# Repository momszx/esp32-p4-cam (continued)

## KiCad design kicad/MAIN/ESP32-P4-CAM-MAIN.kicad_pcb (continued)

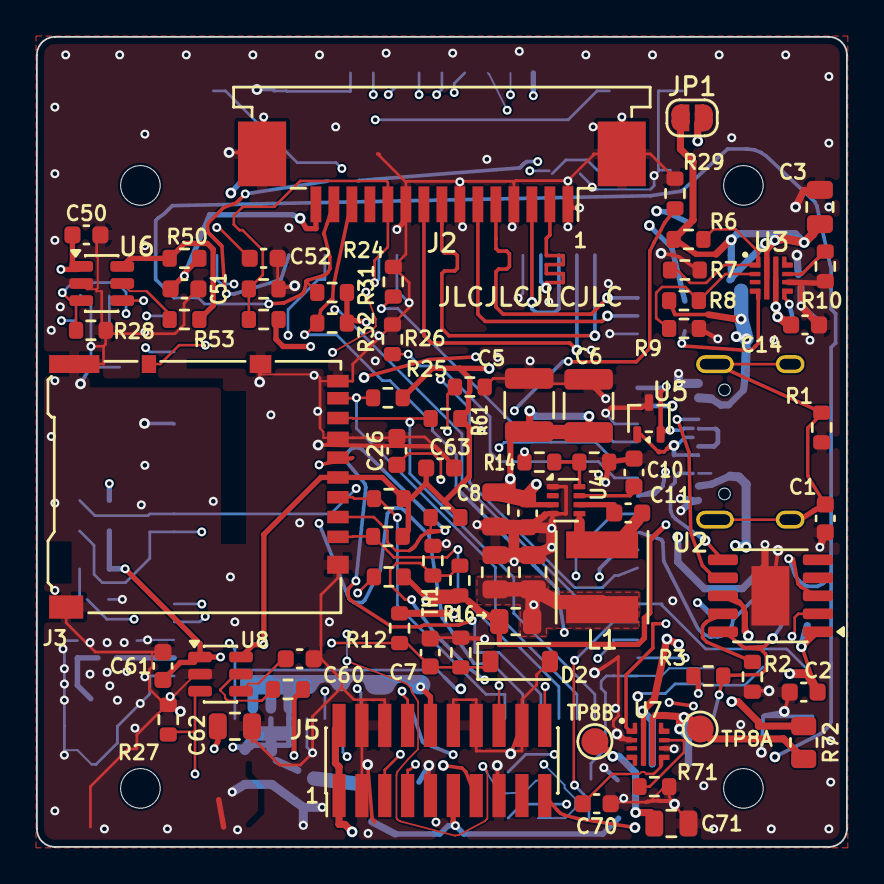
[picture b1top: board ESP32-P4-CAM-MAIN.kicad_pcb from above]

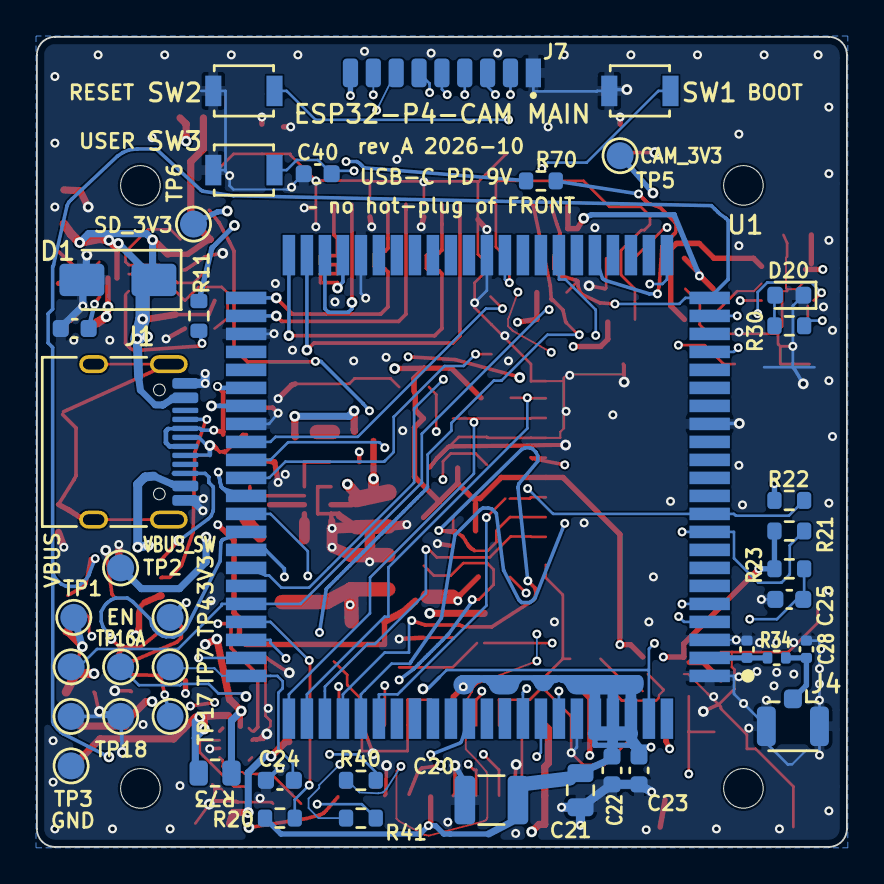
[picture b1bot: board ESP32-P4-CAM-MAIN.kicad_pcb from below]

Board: 4 copper layers, 45.0 x 45.0 mm, 120 parts (42 on the bottom side), 77 nets.

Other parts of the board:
MH1, MH2, MH3, MH4: MountingHole_2.2mm_M2

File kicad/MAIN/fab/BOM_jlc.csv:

Comment,Designator,Footprint,LCSC
4.7nF 200V X7R ±10% 0603,C1,C_0603_1608Metric,C596328
1uF 50V X5R ±10% 0603,"C2,C24,C25,C50,C51",C_0603_1608Metric,C15849
4.7uF 50V X5R ±10% 0805,C3,C_0805_2012Metric,C98192
1nF 50V X7R ±10% 0603,"C4,C52",C_0603_1608Metric,C1588
22uF 25V X5R ±10% 1210,"C5,C6",C_1210_3225Metric,C52306
100nF 50V X7R ±10% 0603,"C7,C9,C11,C22,C23,C26,C40",C_0603_1608Metric,C14663
10uF 25V X5R ±10% 0805,"C8,C21",C_0805_2012Metric,C15850
10nF 50V X7R ±10% 0603,C10,C_0603_1608Metric,C57112
22uF 25V X5R ±20% 0805,"C12,C13",C_0805_2012Metric,C45783
1uF 25V X7R ±10% 0603,C14,C_0603_1608Metric,C29936
47uF 16V X5R ±10% 1210,C20,C_1210_3225Metric,C77101
TVS uni 10V SMA 400W,D1,D_SMA,C134939
LED emerald green 525nm 0603,D20,LED_0603_1608Metric,C12624
USB-C 16P receptacle SMD + 4 shell legs,J1,USB_C_Receptacle_HRO_TYPE-C-31-M-12,C165948
"FPC 15P 1.0mm slide-lock, TOP contact, SMT right angle",J2,TE_1-84953-5_1x15-1MP_P1.0mm_Horizontal,C5164008
U.FL receptacle SMD,J4,U.FL_Hirose_U.FL-R-SMT-1_Vertical,C88374
"Pin header 2x10 1.27mm SMD vertical, insulator 1.0mm, mating pin 4.0mm",J5,PinHeader_2x10_P1.27mm_Vertical_SMD,C41375929
2.2uH ±30% Isat 4.1A Irms 3.1A 29mΩ 4.9x4.9x2.4mm,L1,L_Taiyo-Yuden_NR-50xx,C222926
1MΩ ±1% 0603,R1,R_0603_1608Metric,C22935
6.8kΩ ±1% 0603,R2,R_0603_1608Metric,C23212
10kΩ ±1% 0603,"R3,R9,R11,R15,R20,R21,R22,R23,R28,R33",R_0603_1608Metric,C25804
267kΩ ±1% 0603,R6,R_0603_1608Metric,C22963
100kΩ ±1% 0603,"R7,R24,R25,R26,R27",R_0603_1608Metric,C25803
80.6kΩ ±1% 0603,R8,R_0603_1608Metric,C23249
1.65kΩ ±1% 0603,R10,R_0603_1608Metric,C22845
200kΩ ±1% 0603,R12,R_0603_1608Metric,C25811
54.9kΩ ±1% 0603,R13,R_0603_1608Metric,C23077
31.6kΩ ±1% 0603,R14,R_0603_1608Metric,C25967
0Ω 0805,R16,R_0805_2012Metric,C17477
1kΩ ±1% 0603,"R30,R40,R41",R_0603_1608Metric,C21190
0Ω 0402,R34,R_0402_1005Metric,C17168
0Ω 0603,"R50,R53",R_0603_1608Metric,C21189
47Ω ±1% 0603,R70,R_0603_1608Metric,C23182
Tactile switch SPST 3.0x2.5mm SMD,"SW1,SW2,SW3",SW_SPST_B3U-1000P,C231329
NTC 10kΩ ±1% B3950 0603,TH1,R_0603_1608Metric,C2892547
USB PD3.2 sink controller ESSOP-10,U2,SSOP-10-1EP_3.9x4.9mm_P1mm_EP2.1x3.3mm,C42459160
eFuse 2.7-23V QFN-10 2x2 (RPW),U3,TI_RPW0010A_VQFN-HR-10_2x2mm,C3662799
3.8-30V 3A sync buck FCCM SOT-583,U4,SOT-583-8,C5219272
2-ch ESD 5.5V 0.7pF SOT-323,U5,SOT-323_SC-70,C5350871
Load switch 5.5V 2A SOT-23-6,U6,SOT-23-6,C2681320
